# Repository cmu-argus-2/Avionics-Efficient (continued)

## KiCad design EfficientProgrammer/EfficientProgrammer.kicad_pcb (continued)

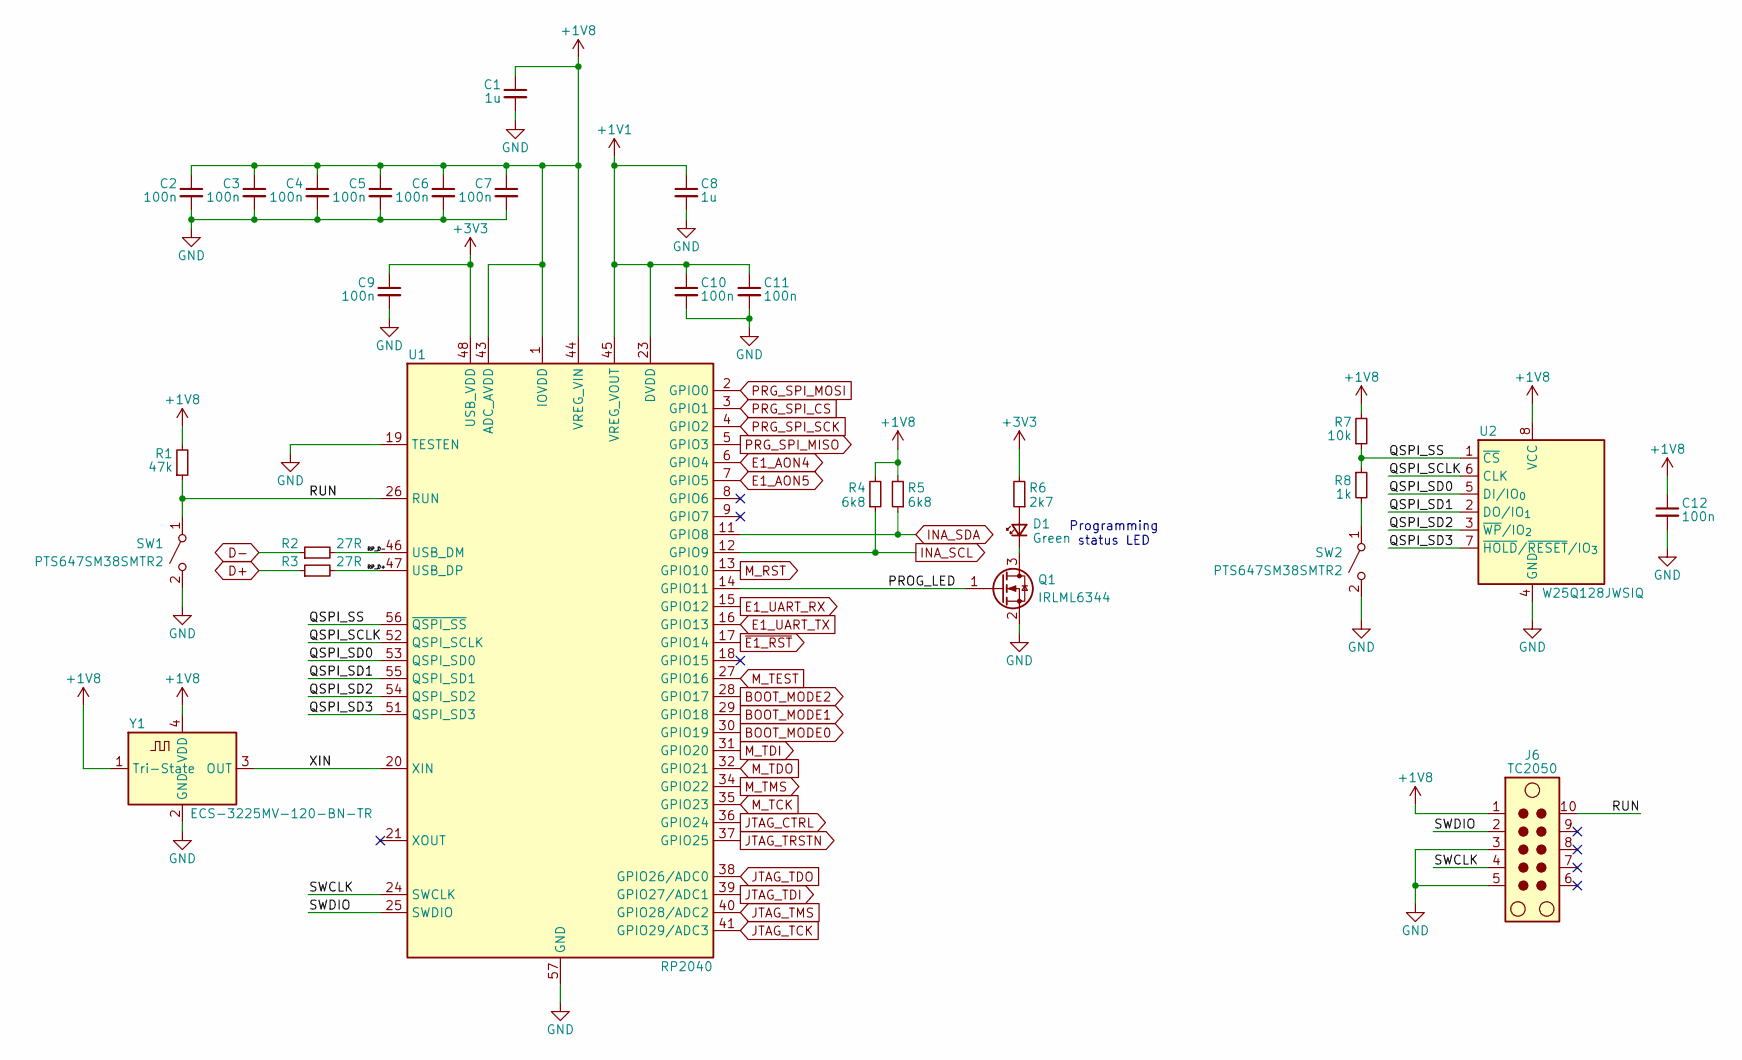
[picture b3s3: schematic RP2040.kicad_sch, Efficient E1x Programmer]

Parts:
C1, C8: 1u; C_0603_1608Metric; MPN C2214844
C2, C3, C4, C5, C6, C7, C9, C10, C11, C12: 100n; C_0603_1608Metric; MPN C307348
D1: Green; LED_0603_1608Metric; MPN C2909774
J6: TC2050; Tag-Connect_TC2050-IDC-NL_2x05_P1.27mm_Vertical
Q1: IRLML6344; SOT-23; MPN C53550
R1: 47k; R_0603_1608Metric; MPN C4151679
R2, R3: 27R; R_0603_1608Metric; MPN C844545
R4, R5: 6k8; R_0603_1608Metric
R6: 2k7; R_0603_1608Metric; MPN C237112
R7: 10k; R_0603_1608Metric; MPN C2479067
R8: 1k; R_0603_1608Metric; MPN C2484712
SW1, SW2: PTS647SM38SMTR2; SW_SPST_PTS647_Sx38; MPN C2689502
U1: RP2040; QFN-56-1EP_7x7mm_P0.4mm_EP3.2x3.2mm; MPN C2040
U2: W25Q128JWSIQ; SOIC-8_5.3x5.3mm_P1.27mm; MPN C2763561
Y1: ECS-3225MV-120-BN-TR; Oscillator_SMD_EuroQuartz_XO32-4Pin_3.2x2.5mm; MPN C405473

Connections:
+1V1: C8.1, C10.1, C11.1, U1.23 (DVDD), U1.45 (VREG_VOUT), U1.50 (DVDD)
+1V8: C1.1, C2.1, C3.1, C4.1, C5.1, C6.1, C7.1, C12.1, J6.1, R1.2, R4.2, R5.2, R7.2, U1.1 (IOVDD), U1.10 (IOVDD), U1.22 (IOVDD), U1.33 (IOVDD), U1.42 (IOVDD), U1.43 (ADC_AVDD), U1.44 (VREG_VIN), U1.49 (IOVDD), U2.8 (VCC), Y1.1 (Tri-State), Y1.4 (VDD); also elsewhere on the board
+3V3: C9.1, R6.2, U1.48 (USB_VDD); also elsewhere on the board
/RP2040/PROG_LED: Q1.1 (G), U1.14 (GPIO11)
/RP2040/QSPI_SCLK: U1.52 (QSPI_SCLK), U2.6 (CLK)
/RP2040/QSPI_SD0: U1.53 (QSPI_SD0), U2.5 (DI/IO_{0})
/RP2040/QSPI_SD1: U1.55 (QSPI_SD1), U2.2 (DO/IO_{1})
/RP2040/QSPI_SD2: U1.54 (QSPI_SD2), U2.3 (~WP/IO_{2})
/RP2040/QSPI_SD3: U1.51 (QSPI_SD3), U2.7 (~HOLD/~RESET/IO_{3})
/RP2040/QSPI_SS: R7.1, R8.1, U1.56 (~QSPI_SS), U2.1 (~CS)
/RP2040/RP_D+: R3.2, U1.47 (USB_DP)
/RP2040/RP_D-: R2.2, U1.46 (USB_DM)
/RP2040/RUN: J6.10, R1.1, SW1.1 (A), U1.26 (RUN)
/RP2040/SWCLK: J6.4, U1.24 (SWCLK)
/RP2040/SWDIO: J6.2, U1.25 (SWDIO)
/RP2040/XIN: U1.20 (XIN), Y1.3 (OUT)
BOOT_MODE0: U1.30 (GPIO19); also elsewhere on the board
BOOT_MODE1: U1.29 (GPIO18); also elsewhere on the board
BOOT_MODE2: U1.28 (GPIO17); also elsewhere on the board
D+: R3.1; also elsewhere on the board
D-: R2.1; also elsewhere on the board
E1_AON4: U1.6 (GPIO4); also elsewhere on the board
E1_AON5: U1.7 (GPIO5); also elsewhere on the board
E1_UART_RX: U1.15 (GPIO12); also elsewhere on the board
E1_UART_TX: U1.16 (GPIO13); also elsewhere on the board
GND: C1.2, C2.2, C3.2, C4.2, C5.2, C6.2, C7.2, C8.2, C9.2, C10.2, C11.2, C12.2, J6.3, J6.5, Q1.2 (S), SW1.2 (B), SW2.2 (B), U1.19 (TESTEN), U1.57 (GND), U2.4 (GND), Y1.2 (GND); also elsewhere on the board
INA_SCL: R4.1, U1.12 (GPIO9); also elsewhere on the board
INA_SDA: R5.1, U1.11 (GPIO8); also elsewhere on the board
JTAG_CTRL: U1.36 (GPIO24); also elsewhere on the board
JTAG_TCK: U1.41 (GPIO29/ADC3); also elsewhere on the board
JTAG_TDI: U1.39 (GPIO27/ADC1); also elsewhere on the board
JTAG_TDO: U1.38 (GPIO26/ADC0); also elsewhere on the board
JTAG_TMS: U1.40 (GPIO28/ADC2); also elsewhere on the board
JTAG_TRSTN: U1.37 (GPIO25); also elsewhere on the board
M_RST: U1.13 (GPIO10); also elsewhere on the board
M_TCK: U1.35 (GPIO23); also elsewhere on the board
M_TDI: U1.31 (GPIO20); also elsewhere on the board
M_TDO: U1.32 (GPIO21); also elsewhere on the board
M_TEST: U1.27 (GPIO16); also elsewhere on the board
M_TMS: U1.34 (GPIO22); also elsewhere on the board
unnamed: D1.2 (A), R6.1
unnamed: D1.1 (K), Q1.3 (D)
unnamed: R8.2, SW2.1 (A)
PRG_SPI_CS: U1.3 (GPIO1); also elsewhere on the board
PRG_SPI_MISO: U1.5 (GPIO3); also elsewhere on the board
PRG_SPI_MOSI: U1.2 (GPIO0); also elsewhere on the board
PRG_SPI_SCK: U1.4 (GPIO2); also elsewhere on the board
~E1_RST: U1.17 (GPIO14); also elsewhere on the board

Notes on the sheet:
Programming status LED

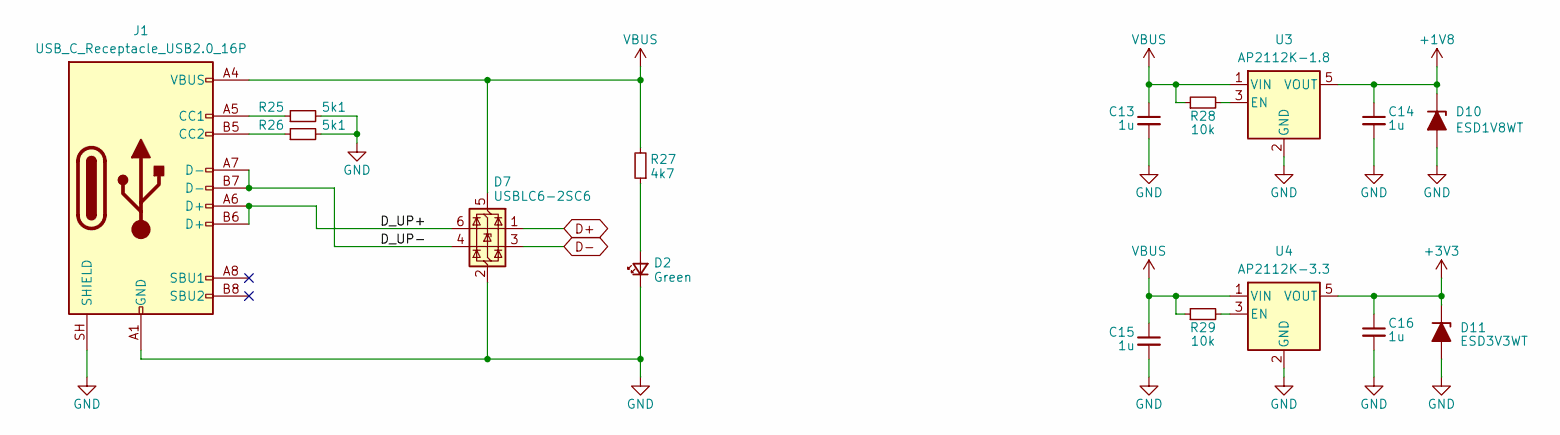
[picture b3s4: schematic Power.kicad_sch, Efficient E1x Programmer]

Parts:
C13, C14, C15, C16: 1u; C_0603_1608Metric; MPN C2214844
D2: Green; LED_0603_1608Metric; MPN C2909774
D7: USBLC6-2SC6; SOT-23-6; MPN C7519
D10: ESD1V8WT; D_SOD-523
D11: ESD3V3WT; D_SOD-523
J1: USB_C_Receptacle_USB2.0_16P; USB_C_Receptacle_GCT_USB4105-xx-A_16P_TopMnt_Horizontal; MPN C3025063
R25, R26: 5k1; R_0603_1608Metric; MPN C2484686
R27: 4k7; R_0603_1608Metric; MPN C2479067
R28, R29: 10k; R_0603_1608Metric; MPN C2479067
U3: AP2112K-1.8; SOT-23-5; MPN C176944
U4: AP2112K-3.3; SOT-23-5; MPN C51118

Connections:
+1V8: C14.1, D10.1 (K), U3.5 (VOUT); also elsewhere on the board
+3V3: C16.1, D11.1 (K), U4.5 (VOUT); also elsewhere on the board
/Power/D_UP+: D7.6 (I/O1), J1.A6 (D+), J1.B6 (D+)
/Power/D_UP-: D7.4 (I/O2), J1.A7 (D-), J1.B7 (D-)
D+: D7.1 (I/O1); also elsewhere on the board
D-: D7.3 (I/O2); also elsewhere on the board
GND: C13.2, C14.2, C15.2, C16.2, D2.1 (K), D7.2 (GND), D10.2 (A), D11.2 (A), J1.A1 (GND), J1.A12 (GND), J1.B1 (GND), J1.B12 (GND), J1.SH (SHIELD), R25.2, R26.2, U3.2 (GND), U4.2 (GND); also elsewhere on the board
unnamed: D2.2 (A), R27.1
unnamed: J1.A5 (CC1), R25.1
unnamed: J1.B5 (CC2), R26.1
unnamed: R28.2, U3.3 (EN)
unnamed: R29.2, U4.3 (EN)
VBUS: C13.1, C15.1, D7.5 (VBUS), J1.A4 (VBUS), J1.A9 (VBUS), J1.B4 (VBUS), J1.B9 (VBUS), R27.2, R28.1, R29.1, U3.1 (VIN), U4.1 (VIN)

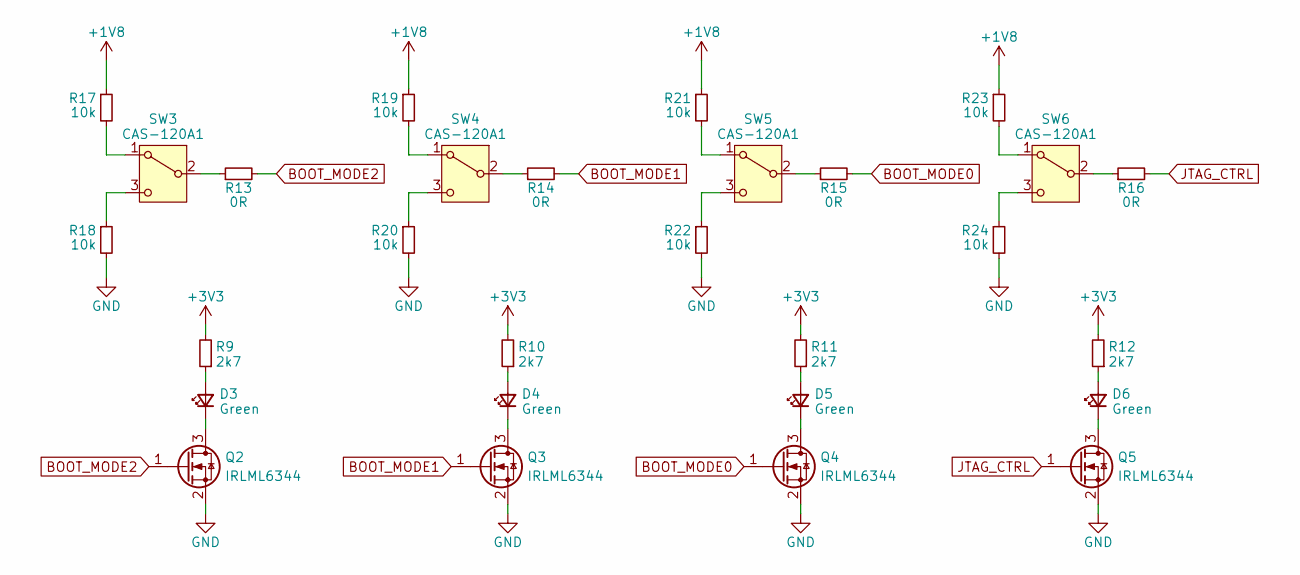
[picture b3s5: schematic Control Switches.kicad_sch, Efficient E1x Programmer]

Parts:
D3, D4, D5, D6: Green; LED_0603_1608Metric; MPN C2909774
Q2, Q3, Q4, Q5: IRLML6344; SOT-23; MPN C53550
R9, R10, R11, R12: 2k7; R_0603_1608Metric; MPN C237112
R13, R14, R15, R16: 0R; R_0603_1608Metric; MPN C844915
R17, R18, R19, R20, R21, R22, R23, R24: 10k; R_0603_1608Metric; MPN C2484712
SW3, SW4, SW5, SW6: CAS-120A1; Nidec_Copal_CAS-120A; MPN C5962834

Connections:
+1V8: R17.1, R19.1, R21.1, R23.1; also elsewhere on the board
+3V3: R9.2, R10.2, R11.2, R12.2; also elsewhere on the board
BOOT_MODE0: Q4.1 (G), R15.2; also elsewhere on the board
BOOT_MODE1: Q3.1 (G), R14.2; also elsewhere on the board
BOOT_MODE2: Q2.1 (G), R13.2; also elsewhere on the board
GND: Q2.2 (S), Q3.2 (S), Q4.2 (S), Q5.2 (S), R18.2, R20.2, R22.2, R24.2; also elsewhere on the board
JTAG_CTRL: Q5.1 (G), R16.2; also elsewhere on the board
unnamed: D3.2 (A), R9.1
unnamed: D3.1 (K), Q2.3 (D)
unnamed: D4.2 (A), R10.1
unnamed: D4.1 (K), Q3.3 (D)
unnamed: D5.2 (A), R11.1
unnamed: D5.1 (K), Q4.3 (D)
unnamed: D6.2 (A), R12.1
unnamed: D6.1 (K), Q5.3 (D)
unnamed: R17.2, SW3.1 (A)
unnamed: R13.1, SW3.2 (B)
unnamed: R18.1, SW3.3 (C)
unnamed: R19.2, SW4.1 (A)
unnamed: R14.1, SW4.2 (B)
unnamed: R20.1, SW4.3 (C)
unnamed: R21.2, SW5.1 (A)
unnamed: R15.1, SW5.2 (B)
unnamed: R22.1, SW5.3 (C)
unnamed: R23.2, SW6.1 (A)
unnamed: R16.1, SW6.2 (B)
unnamed: R24.1, SW6.3 (C)

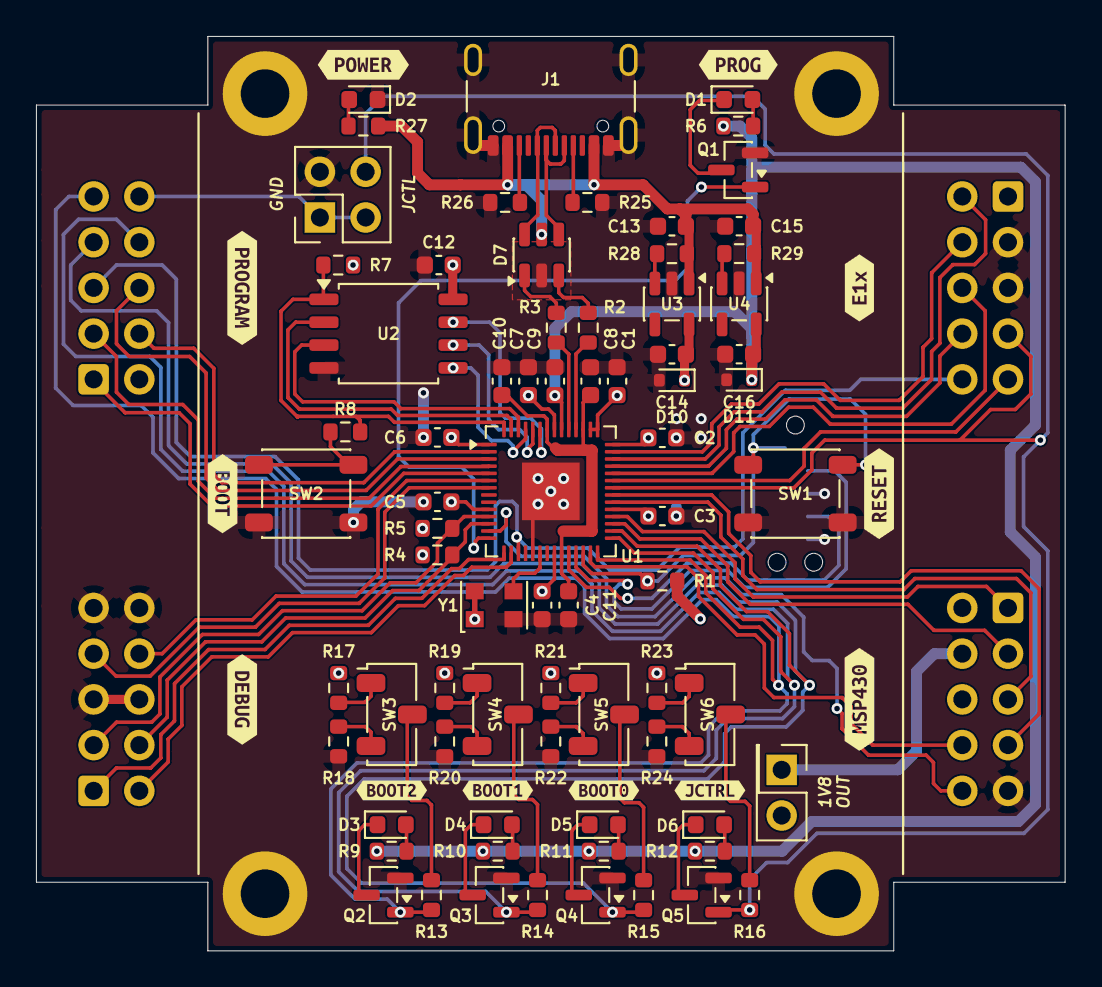
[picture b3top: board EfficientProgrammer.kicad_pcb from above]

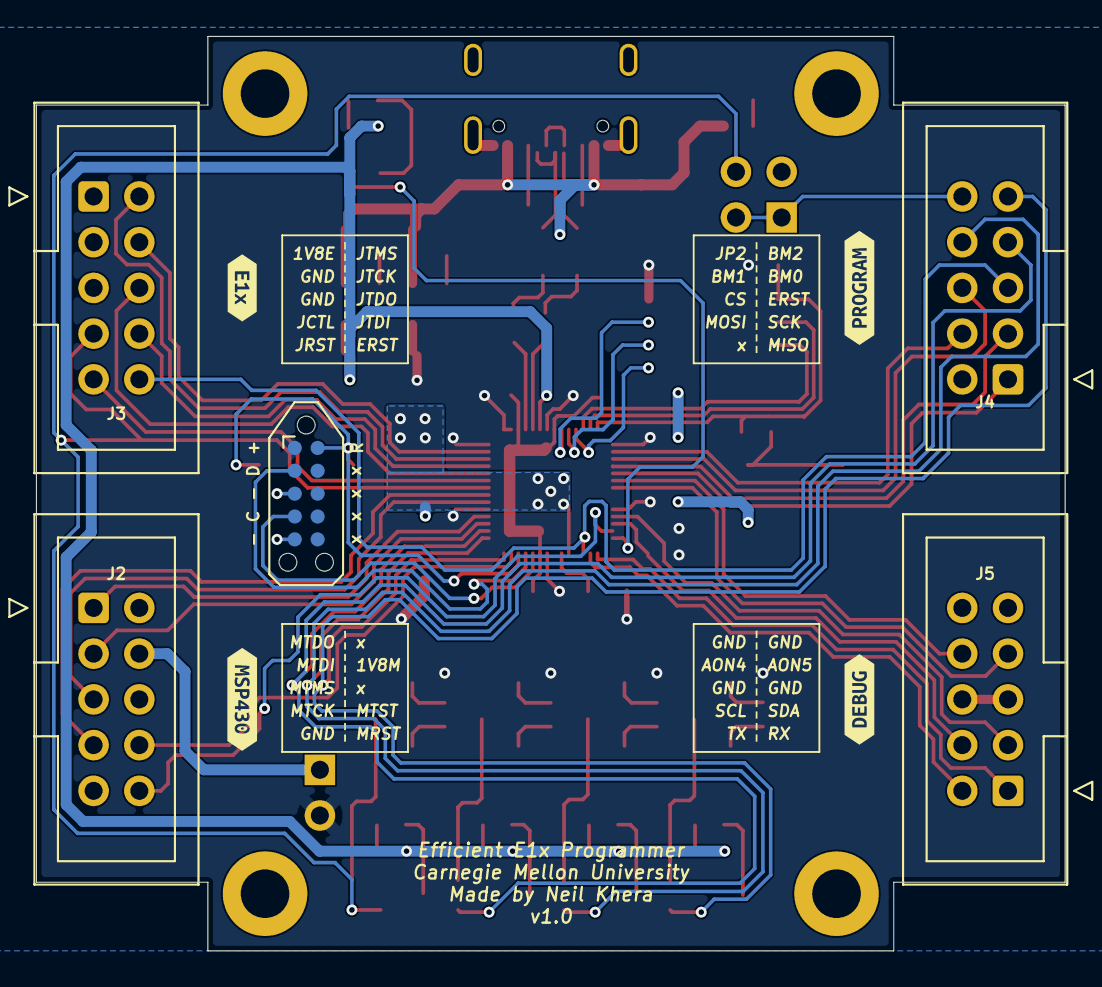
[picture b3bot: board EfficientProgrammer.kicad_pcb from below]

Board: 2 copper layers, 57.1 x 50.8 mm, 98 parts (9 on the bottom side), 78 nets.

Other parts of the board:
kibuzzard-6A02A791: G***; kibuzzard-6A02A791
kibuzzard-6A0274AA: G***; kibuzzard-6A0274AA
kibuzzard-69DC4E32: G***; kibuzzard-69DC4E32
kibuzzard-69DC4EF8: G***; kibuzzard-69DC4EF8
kibuzzard-69DC4F08: G***; kibuzzard-69DC4F08
kibuzzard-69DF12FD: G***; kibuzzard-69DF12FD
kibuzzard-69DF14E7: G***; kibuzzard-69DF14E7
kibuzzard-69DF129C: G***; kibuzzard-69DF129C
kibuzzard-69DF176E: G***; kibuzzard-69DF176E
kibuzzard-69DF179A: G***; kibuzzard-69DF179A
kibuzzard-69DF205B, kibuzzard-69DF205B#2: G***; kibuzzard-69DF205B
kibuzzard-69DF3352, kibuzzard-69DF3352#2: G***; kibuzzard-69DF3352
kibuzzard-69E00355, kibuzzard-69E00355#2: G***; kibuzzard-69E00355

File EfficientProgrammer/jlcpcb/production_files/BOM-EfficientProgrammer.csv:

Comment,Designator,Footprint,LCSC,Quantity
0R,"R13,R14,R15,R16",R_0603_1608Metric,C844915,4
100n,"C10,C11,C12,C2,C3,C4,C5,C6,C7,C9",C_0603_1608Metric,C307348,10
10k,"R17,R18,R19,R20,R21,R22,R23,R24,R28,R29,R7",R_0603_1608Metric,C2479067,11
1k,R8,R_0603_1608Metric,C2484712,1
1u,"C1,C13,C14,C15,C16,C8",C_0603_1608Metric,C2214844,6
27R,"R2,R3",R_0603_1608Metric,C844545,2
2k7,"R10,R11,R12,R6,R9",R_0603_1608Metric,C4333774,5
47k,R1,R_0603_1608Metric,C4151679,1
4k7,R27,R_0603_1608Metric,C4293273,1
5k1,"R25,R26",R_0603_1608Metric,C2484686,2
6k8,"R4,R5",R_0603_1608Metric,C844805,2
AP2112K-1.8,U3,SOT-23-5,C176944,1
AP2112K-3.3,U4,SOT-23-5,C51118,1
CAS-120A1,"SW3,SW4,SW5,SW6",Nidec_Copal_CAS-120A,C5962834,4
ECS-3225MV-120-BN-TR,Y1,Oscillator_SMD_EuroQuartz_XO32-4Pin_3.2x2.5mm,C405473,1
Green,"D1,D2,D3,D4,D5,D6",LED_0603_1608Metric,C2909774,6
IRLML6344,"Q1,Q2,Q3,Q4,Q5",SOT-23,C53550,5
PTS647SM38SMTR2,"SW1,SW2",SW_SPST_PTS647_Sx38,C2689502,2
RP2040,U1,QFN-56-1EP_7x7mm_P0.4mm_EP3.2x3.2mm,C2040,1
USBLC6-2SC6,D7,SOT-23-6,C7519,1
USB_C_Receptacle_USB2.0_16P,J1,USB_C_Receptacle_GCT_USB4105-xx-A_16P_TopMnt_Horizontal,C3025063,1
W25Q128JWSIQ,U2,SOIC-8_5.3x5.3mm_P1.27mm,C2763561,1
Conn_02x02,J7,PinHeader_2x02_P2.54mm_Vertical,,1
ESD3V3WT,D11,D_SOD-523,,1
ESD1V8WT,D10,D_SOD-523,,1
Conn_02x01,J8,PinHeader_2x01_P2.54mm_Vertical,,1
SBH11-PBPC-D05-ST-BK,J2,IDC-Header_2x05_P2.54mm_Vertical,,1
SBH11-PBPC-D05-ST-BK,J3,IDC-Header_2x05_P2.54mm_Vertical,,1
SBH11-PBPC-D05-ST-BK,J5,IDC-Header_2x05_P2.54mm_Vertical,,1
SBH11-PBPC-D05-ST-BK,J4,IDC-Header_2x05_P2.54mm_Vertical,,1

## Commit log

2026-05-19 Initial Upload
2026-05-19 Updated Files
2026-05-19 Upload BOMs
